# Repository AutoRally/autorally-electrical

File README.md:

# autorally-electrical
Electrical System for the AutoRally project

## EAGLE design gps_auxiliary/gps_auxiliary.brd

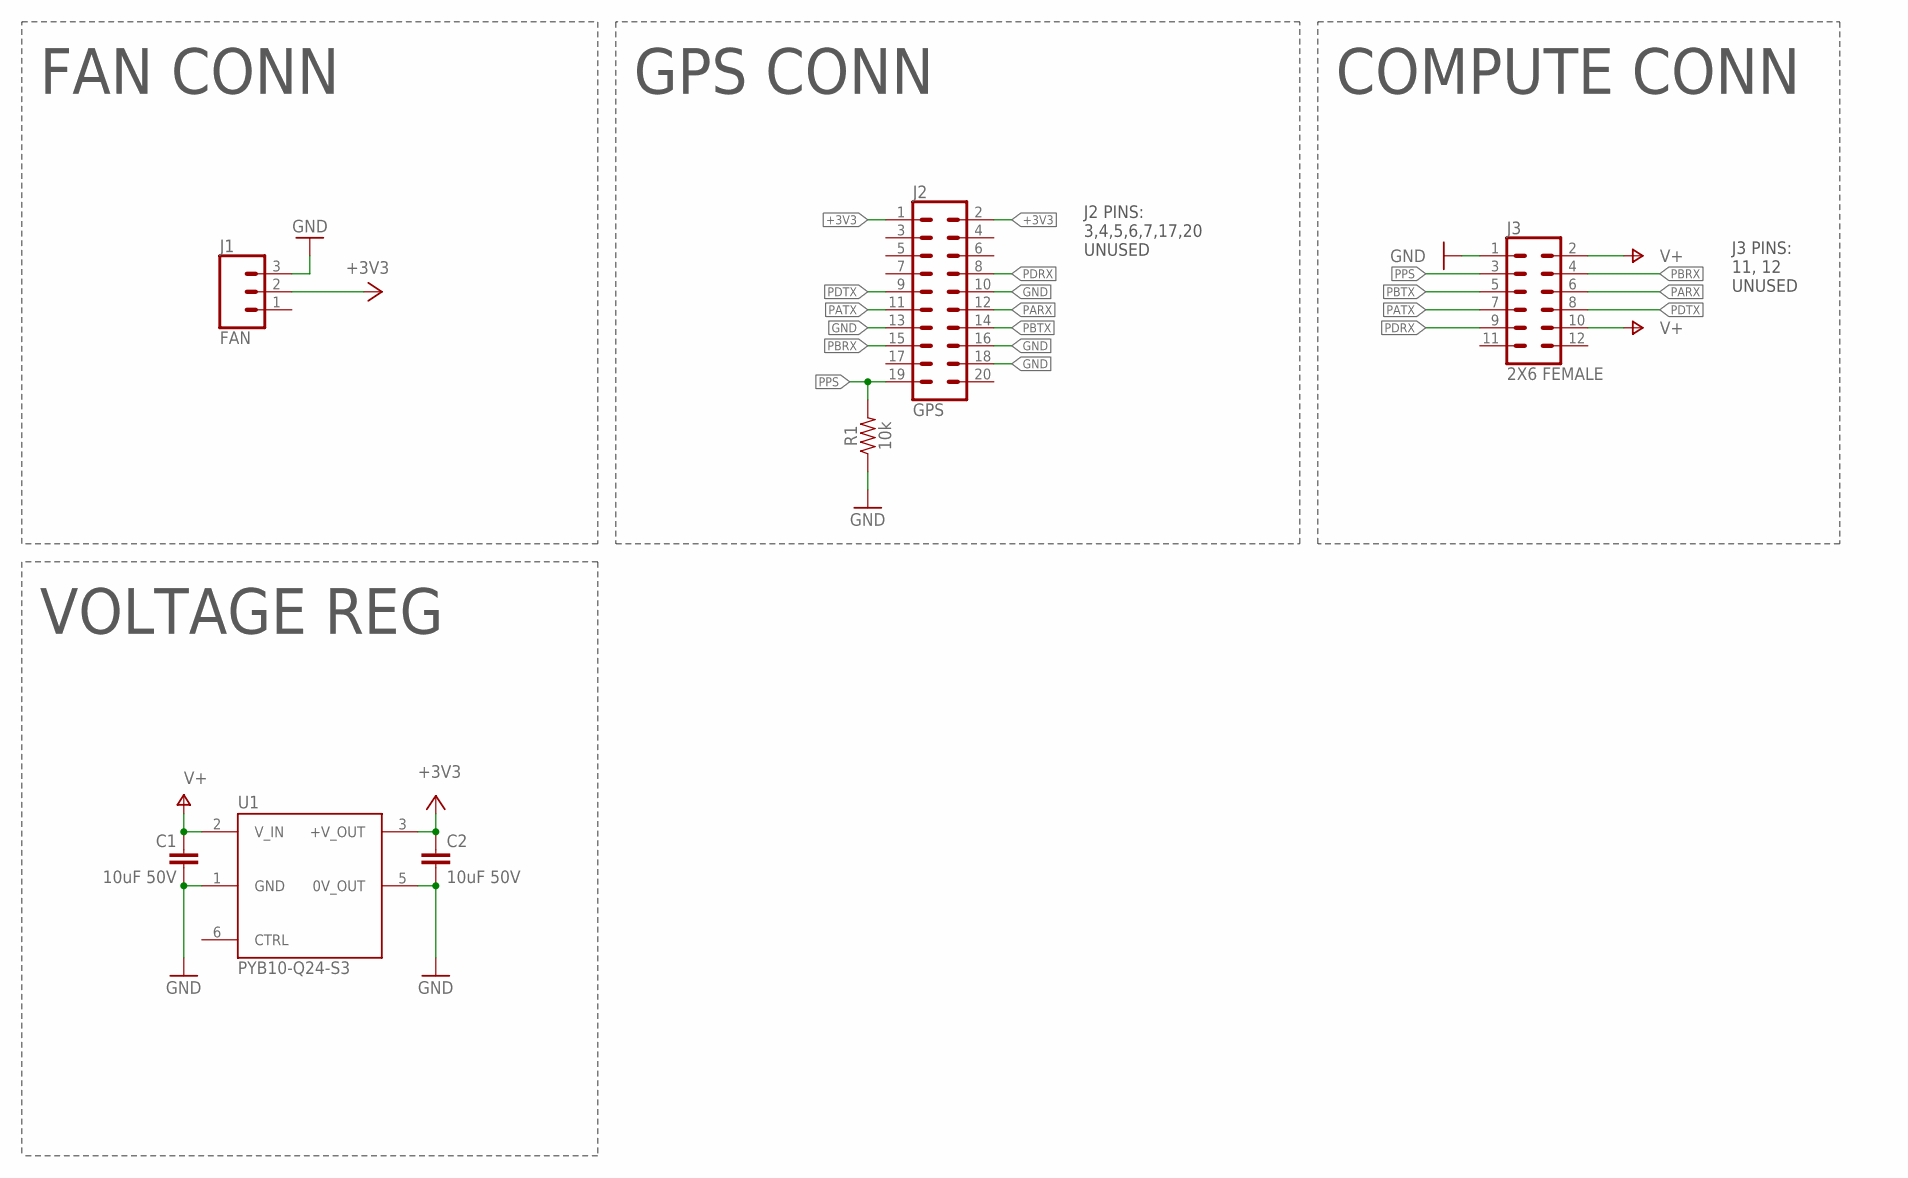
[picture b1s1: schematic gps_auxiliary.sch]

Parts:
C1, C2: 10uF 50V; CAP-PTH-5MM
J1: FAN; ED700
J2: GPS; EHT-110-01-S-D
J3: 2X6 FEMALE; 2X6
R1: 10k; AXIAL-0.3
U1: PYB10-Q24-S3; PYB10

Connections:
+3V3: C2.1, J1.2, J2.1, J2.2, U1.3 (+V_OUT)
GND: C1.2, C2.2, J1.3, J2.10, J2.13, J2.16, J2.18, J3.1, R1.1, U1.1 (GND), U1.5 (0V_OUT)
PARX: J2.12, J3.6
PATX: J2.11, J3.7
PBRX: J2.15, J3.4
PBTX: J2.14, J3.5
PDRX: J2.8, J3.9
PDTX: J2.9, J3.8
PPS: J2.19, J3.3, R1.2
V+: C1.1, J3.2, J3.10, U1.2 (V_IN)

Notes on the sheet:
J2 PINS: 3,4,5,6,7,17,20 UNUSED
J3 PINS: 11, 12 UNUSED
FAN CONN
GPS CONN
COMPUTE CONN
VOLTAGE REG

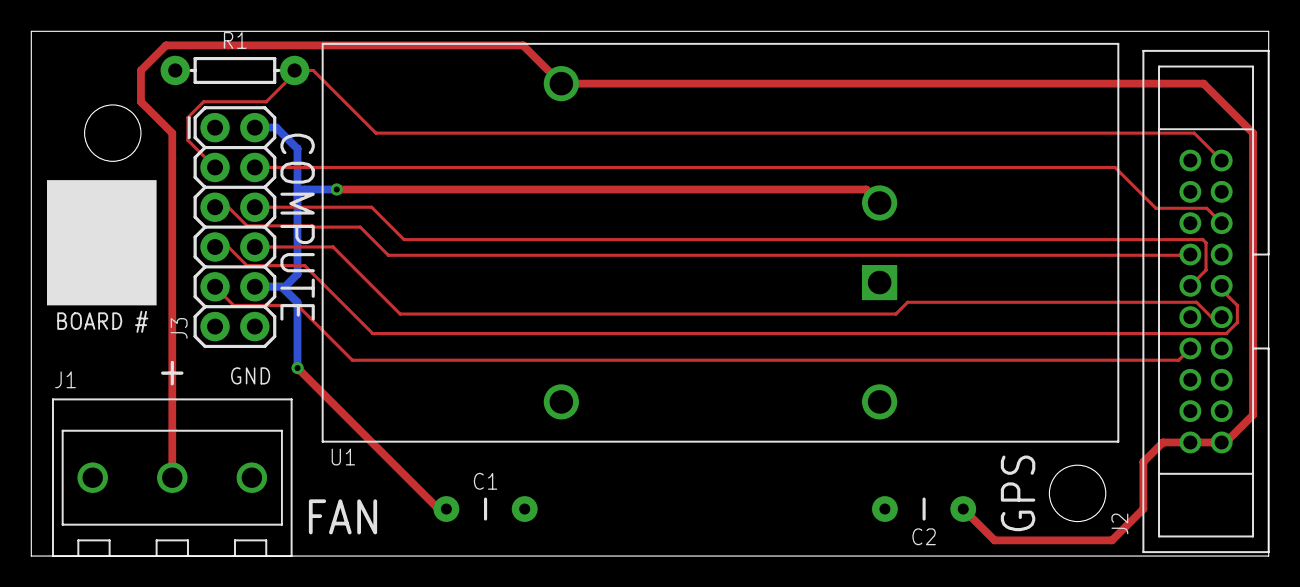
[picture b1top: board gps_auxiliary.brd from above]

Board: 2 copper layers, 79.0 x 33.5 mm, 7 parts (0 on the bottom side), 10 nets.

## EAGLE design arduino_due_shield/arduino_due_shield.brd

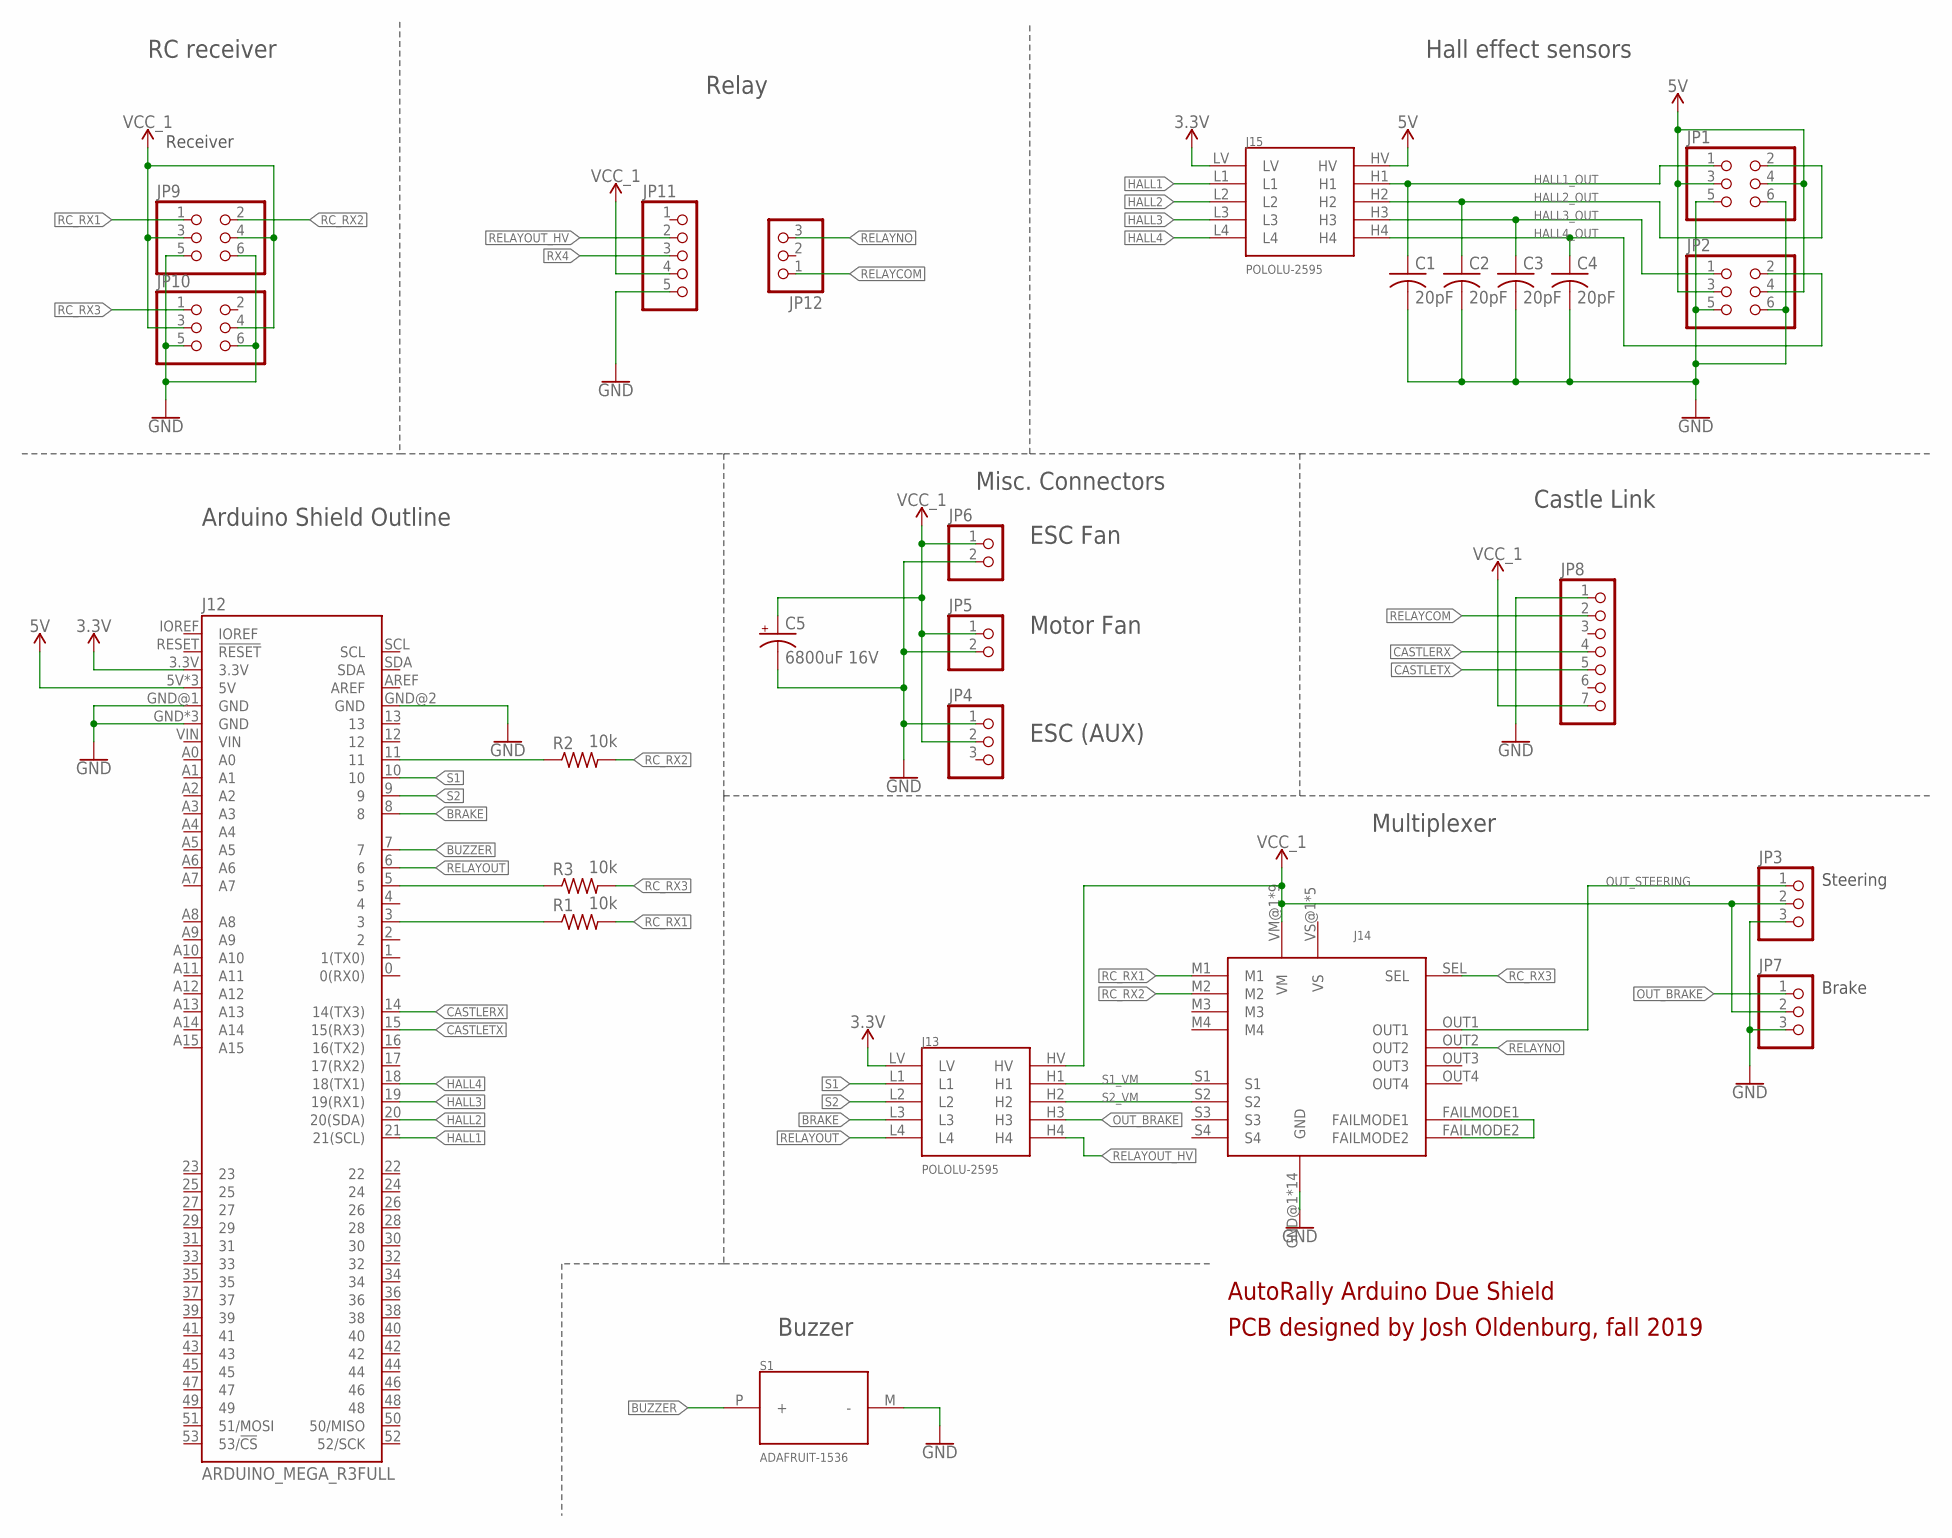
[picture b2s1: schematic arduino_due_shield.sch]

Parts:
C1, C2, C3, C4: 20pF; C025-030X050
C5: 6800uF 16V; E7,5-16
J12: ARDUINO_MEGA_R3FULL; ARDUINO_MEGA_NO_SILK
J13, J15: POLOLU-2595; POLOLU-2595-PTH
J14: POLOLU-2807; POLOLU-2807-PTH
JP1, JP2, JP9, JP10: PINHD-2X3; 2X03
JP3, JP4, JP7, JP12: PINHD-1X3; 1X03
JP5, JP6: PINHD-1X2; 1X02
JP8: PINHD-1X7; 1X07
JP11: PINHD-1X5; 1X05
R1, R2, R3: 10k; 0204/7
S1: ADAFRUIT-1536

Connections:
3.3V: J12.3.3V, J13.LV, J15.LV
5V: J12.5V, J12.5V@1 (5V), J12.5V@2 (5V), J15.HV, JP1.3, JP1.4, JP2.3, JP2.4
BRAKE: J12.8, J13.L3
BUZZER: J12.7, S1.P (+)
CASTLERX: J12.14 (14(TX3)), JP8.4
CASTLETX: J12.15 (15(RX3)), JP8.5
GND: C1.2, C2.2, C3.2, C4.2, C5.-, J12.GND, J12.GND@1 (GND), J12.GND@2 (GND), J12.GND@3 (GND), J12.GND@4 (GND), J14.GND@1 (GND), J14.GND@2 (GND), J14.GND@3 (GND), J14.GND@4 (GND), J14.GND@5 (GND), J14.GND@6 (GND), J14.GND@7 (GND), J14.GND@8 (GND), J14.GND@9 (GND), J14.GND@10 (GND), J14.GND@11 (GND), J14.GND@12 (GND), J14.GND@13 (GND), J14.GND@14 (GND), JP1.5, JP1.6, JP2.5, JP2.6, JP3.3, JP4.1, JP5.2, JP6.2, JP7.3, JP8.1, JP9.5, JP9.6, JP10.5, JP10.6, JP11.5, S1.M (-)
HALL1: J12.21 (21(SCL)), J15.L1
HALL1_OUT: C1.1, J15.H1, JP1.1
HALL2: J12.20 (20(SDA)), J15.L2
HALL2_OUT: C2.1, J15.H2, JP1.2
HALL3: J12.19 (19(RX1)), J15.L3
HALL3_OUT: C3.1, J15.H3, JP2.1
HALL4: J12.18 (18(TX1)), J15.L4
HALL4_OUT: C4.1, J15.H4, JP2.2
unnamed: J12.11, R2.1
unnamed: J14.FAILMODE1, J14.FAILMODE2
unnamed: J12.5, R3.1
unnamed: J12.3, R1.1
OUT_BRAKE: J13.H3, JP7.1
OUT_STEERING: J14.OUT1, JP3.1
RC_RX1: J14.M1, JP9.1, R1.2
RC_RX2: J14.M2, JP9.2, R2.2
RC_RX3: J14.SEL, JP10.1, R3.2
RC_RX4: JP10.2, JP11.3
RELAYCOM: JP8.2, JP12.1
RELAYNO: J14.OUT2, JP12.3
RELAYOUT: J12.6, J13.L4
RELAYOUT_HV: J13.H4, JP11.2
S1: J12.10, J13.L1
S1_VM: J13.H1, J14.S1
S2: J12.9, J13.L2
S2_VM: J13.H2, J14.S2
VCC_2: C5.+, J13.HV, J14.VM@1 (VM), J14.VM@2 (VM), J14.VM@3 (VM), J14.VM@4 (VM), J14.VM@5 (VM), J14.VM@6 (VM), J14.VM@7 (VM), J14.VM@8 (VM), J14.VM@9 (VM), JP3.2, JP4.2, JP5.1, JP6.1, JP7.2, JP8.7, JP9.3, JP9.4, JP10.3, JP10.4, JP11.4

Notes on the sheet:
ESC Fan
Motor Fan
ESC (AUX)
Steering
Brake
Hall effect sensors
Receiver
Relay
Castle Link
AutoRally Arduino Due Shield
PCB designed by Josh Oldenburg, fall 2019
Arduino Shield Outline
Buzzer
RC receiver
Misc. Connectors
Multiplexer

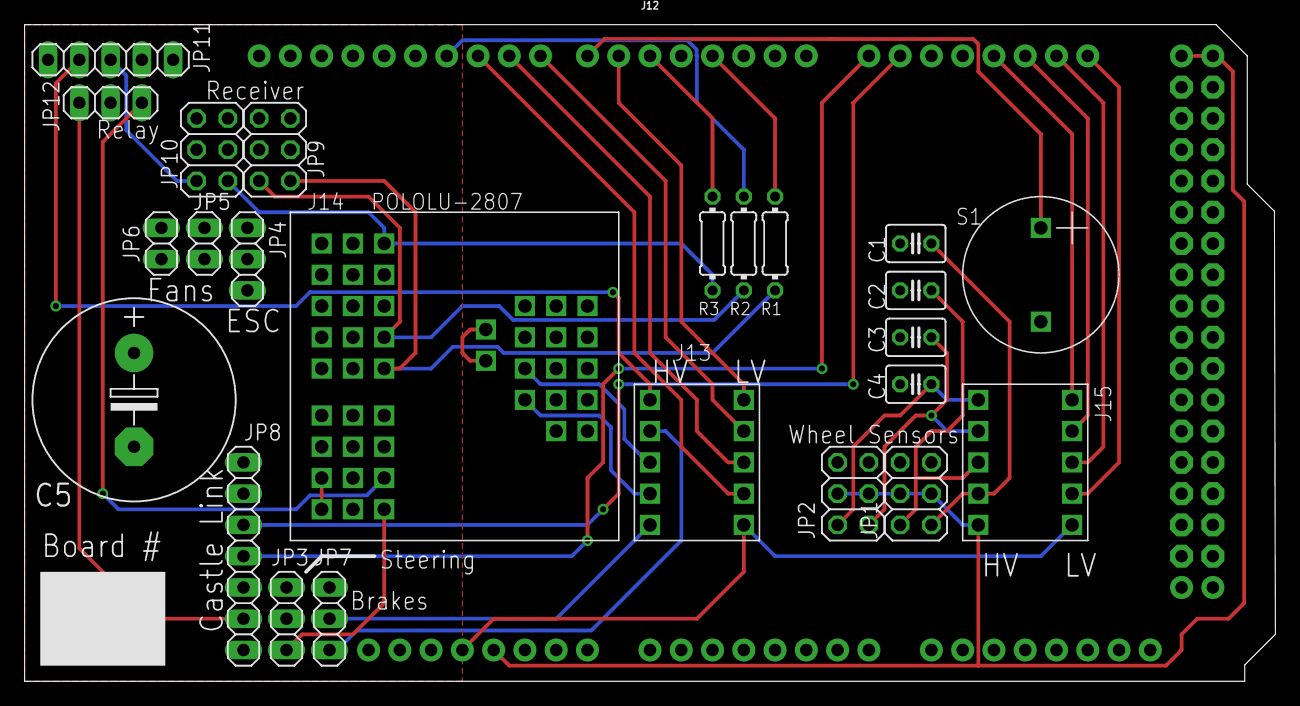
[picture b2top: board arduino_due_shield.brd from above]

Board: 2 copper layers, 101.6 x 53.3 mm, 25 parts (0 on the bottom side), 34 nets.

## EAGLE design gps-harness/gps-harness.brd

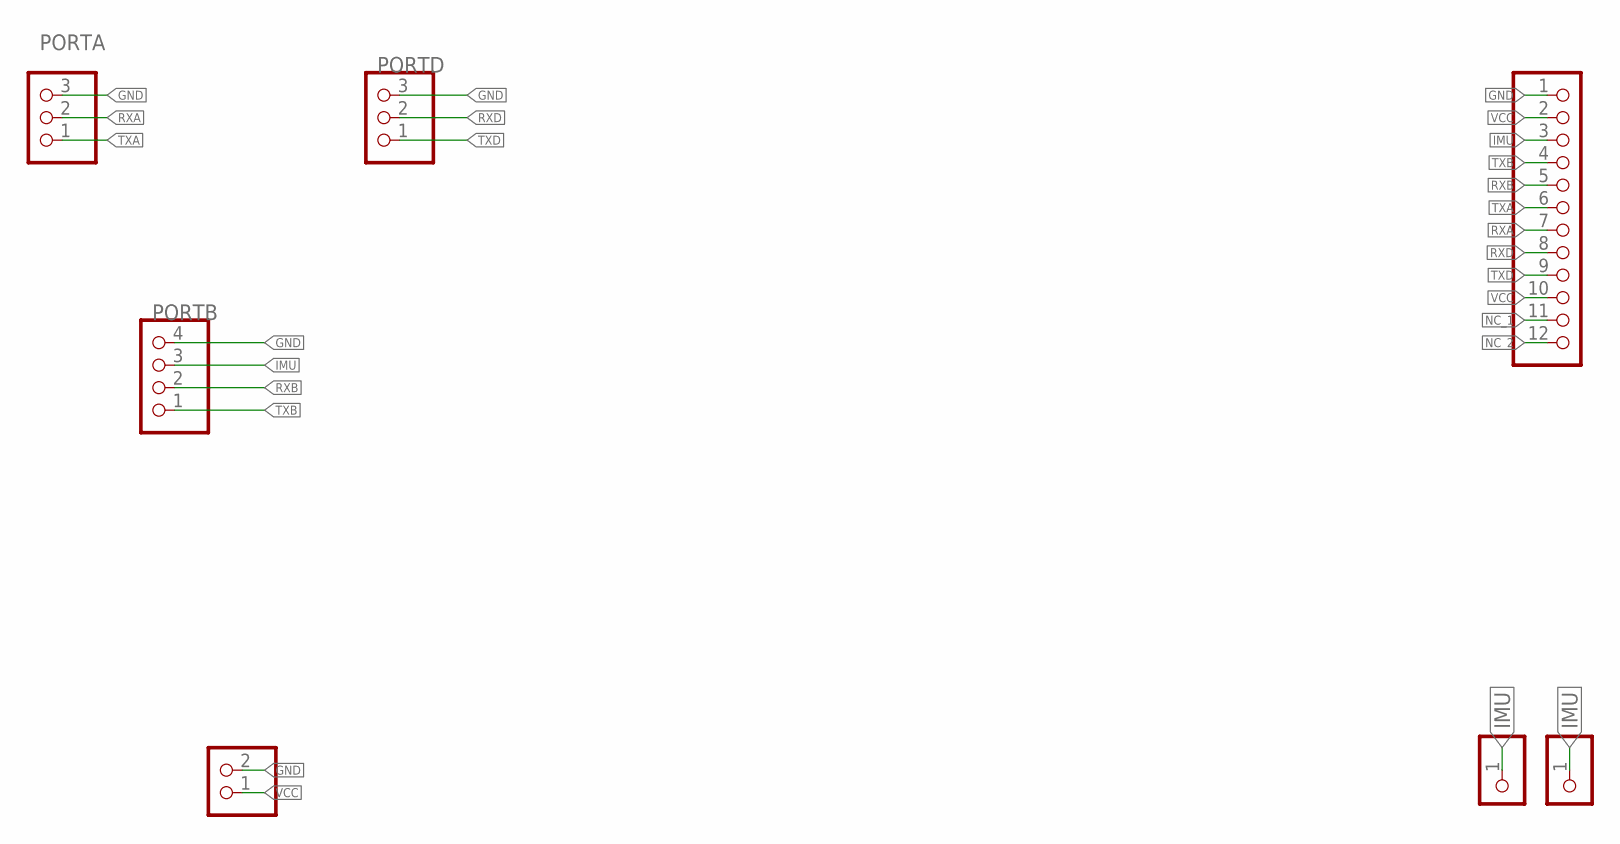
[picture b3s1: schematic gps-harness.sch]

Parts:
BATTERY: PINHD-1X2; 1X02
GPIO: PINHD-1X12; 1X12
IMU: PINHD-1X1; 1X01
PORTA: PINHD-1X3; 1X03
PORTB: PINHD-1X4; 1X04
PORTD: PINHD-1X3; 1X03
TSY: PINHD-1X1; 1X01

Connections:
GND: BATTERY.2, GPIO.1, PORTA.3, PORTB.4, PORTD.3
IMU: GPIO.3, IMU.1, PORTB.3, TSY.1
NC_1: GPIO.11
NC_2: GPIO.12
RXA: GPIO.7, PORTA.2
RXB: GPIO.5, PORTB.2
RXD: GPIO.8, PORTD.2
TXA: GPIO.6, PORTA.1
TXB: GPIO.4, PORTB.1
TXD: GPIO.9, PORTD.1
VCC: BATTERY.1, GPIO.2, GPIO.10

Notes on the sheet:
PORTA
PORTB
PORTD

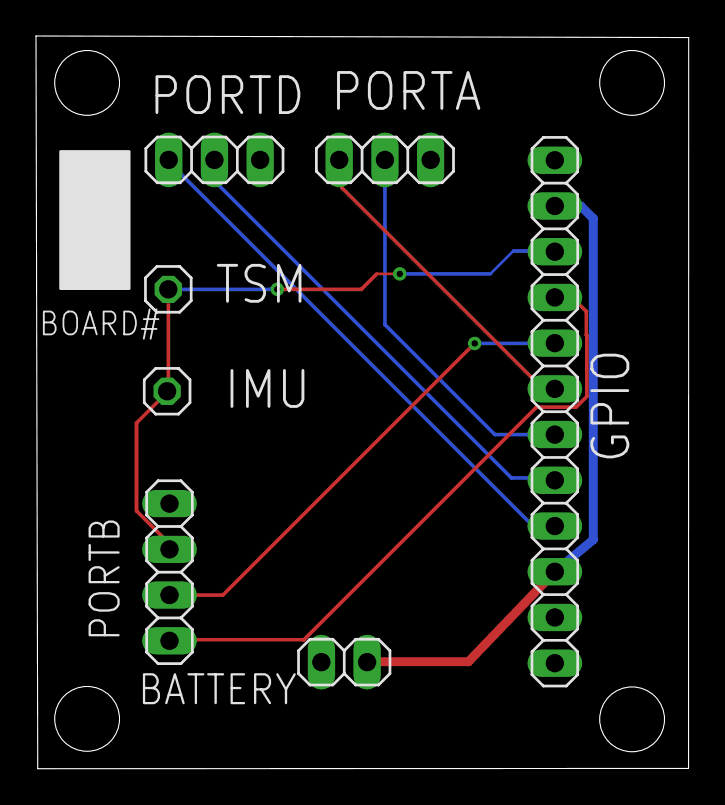
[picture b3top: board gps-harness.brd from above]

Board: 2 copper layers, 36.3 x 40.7 mm, 7 parts (0 on the bottom side), 9 nets.

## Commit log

2019-08-30 Initial library development
    Added 3v3 Power Supply
    Added 3 pos screw terminal
    Added 20 pos locking connector
2019-09-10 Added parts list, added 6x2 connector
2019-09-16 Added 6x2 connector, finished schematic
2019-09-16 Finished GPS board design
2019-09-19 Increased distance between PPS and increased power routing
2019-09-19 Checked RJ DRC, increased Via size
2019-09-24 Changed board dimensions to fit existing
2019-09-27 Added capacitor to library and board
2019-09-27 Reformated part list, generated gerbers
2019-10-01 gps-harness
2019-10-04 Fixed the width of the wires for battery and trying to do the mounting holes
2019-10-04 Trying to choose the connector
2019-10-05 Mounting holes
2019-10-15 Add Due shield initial design
2019-10-21 Add CSV File
2019-10-24 Change Schematic to Parts by parts
2019-10-24 Schenatic Diagram
2019-10-27 Reroute the board
2019-10-29 Add GND Plane
2019-10-30 Add GND PLane & clearify the fastner of the right bottom driller, regorup rhe schematic
2019-11-07 Modify the place of the left bottom mounting hole; Unify the width of the wires; clear up the GND line since there's a ground plane
2019-11-18 Ensure every wire eidth are the same
2019-12-15 Finish schematic and PCB design
2019-12-15 Add missing RC_RX4 net

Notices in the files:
parts and their libraries:
SparkFun-Boards: Licensing: Creative Commons ShareAlike 4.0 International - https://creativecommons.org/licenses/by-sa/4.0
